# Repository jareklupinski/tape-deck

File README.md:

# tape-deck
a user-unfriendly design

```
to play music, just give it a tape.
tape-deck plays to end of the tape,
reverses, and plays the other side.
```

```
HOW DOES ONE PAUSE / STOP THE TAPE?
you should finish what you started.
```

```
HOW DO I MAKE IT LOUDER OR QUIETER?
listen to louder or quieter albums.
```

```
CAN I FASTFORWARD OR REWIND AT ALL?
the artists who recorded this album
want you to listen to it like this.
```

thank you

# MAKING OF

Circuit Board Design

Schematic

Enclosure

Code
Derived from https://github.com/elehobica/pico_crp42602y_ctrl/tree/main

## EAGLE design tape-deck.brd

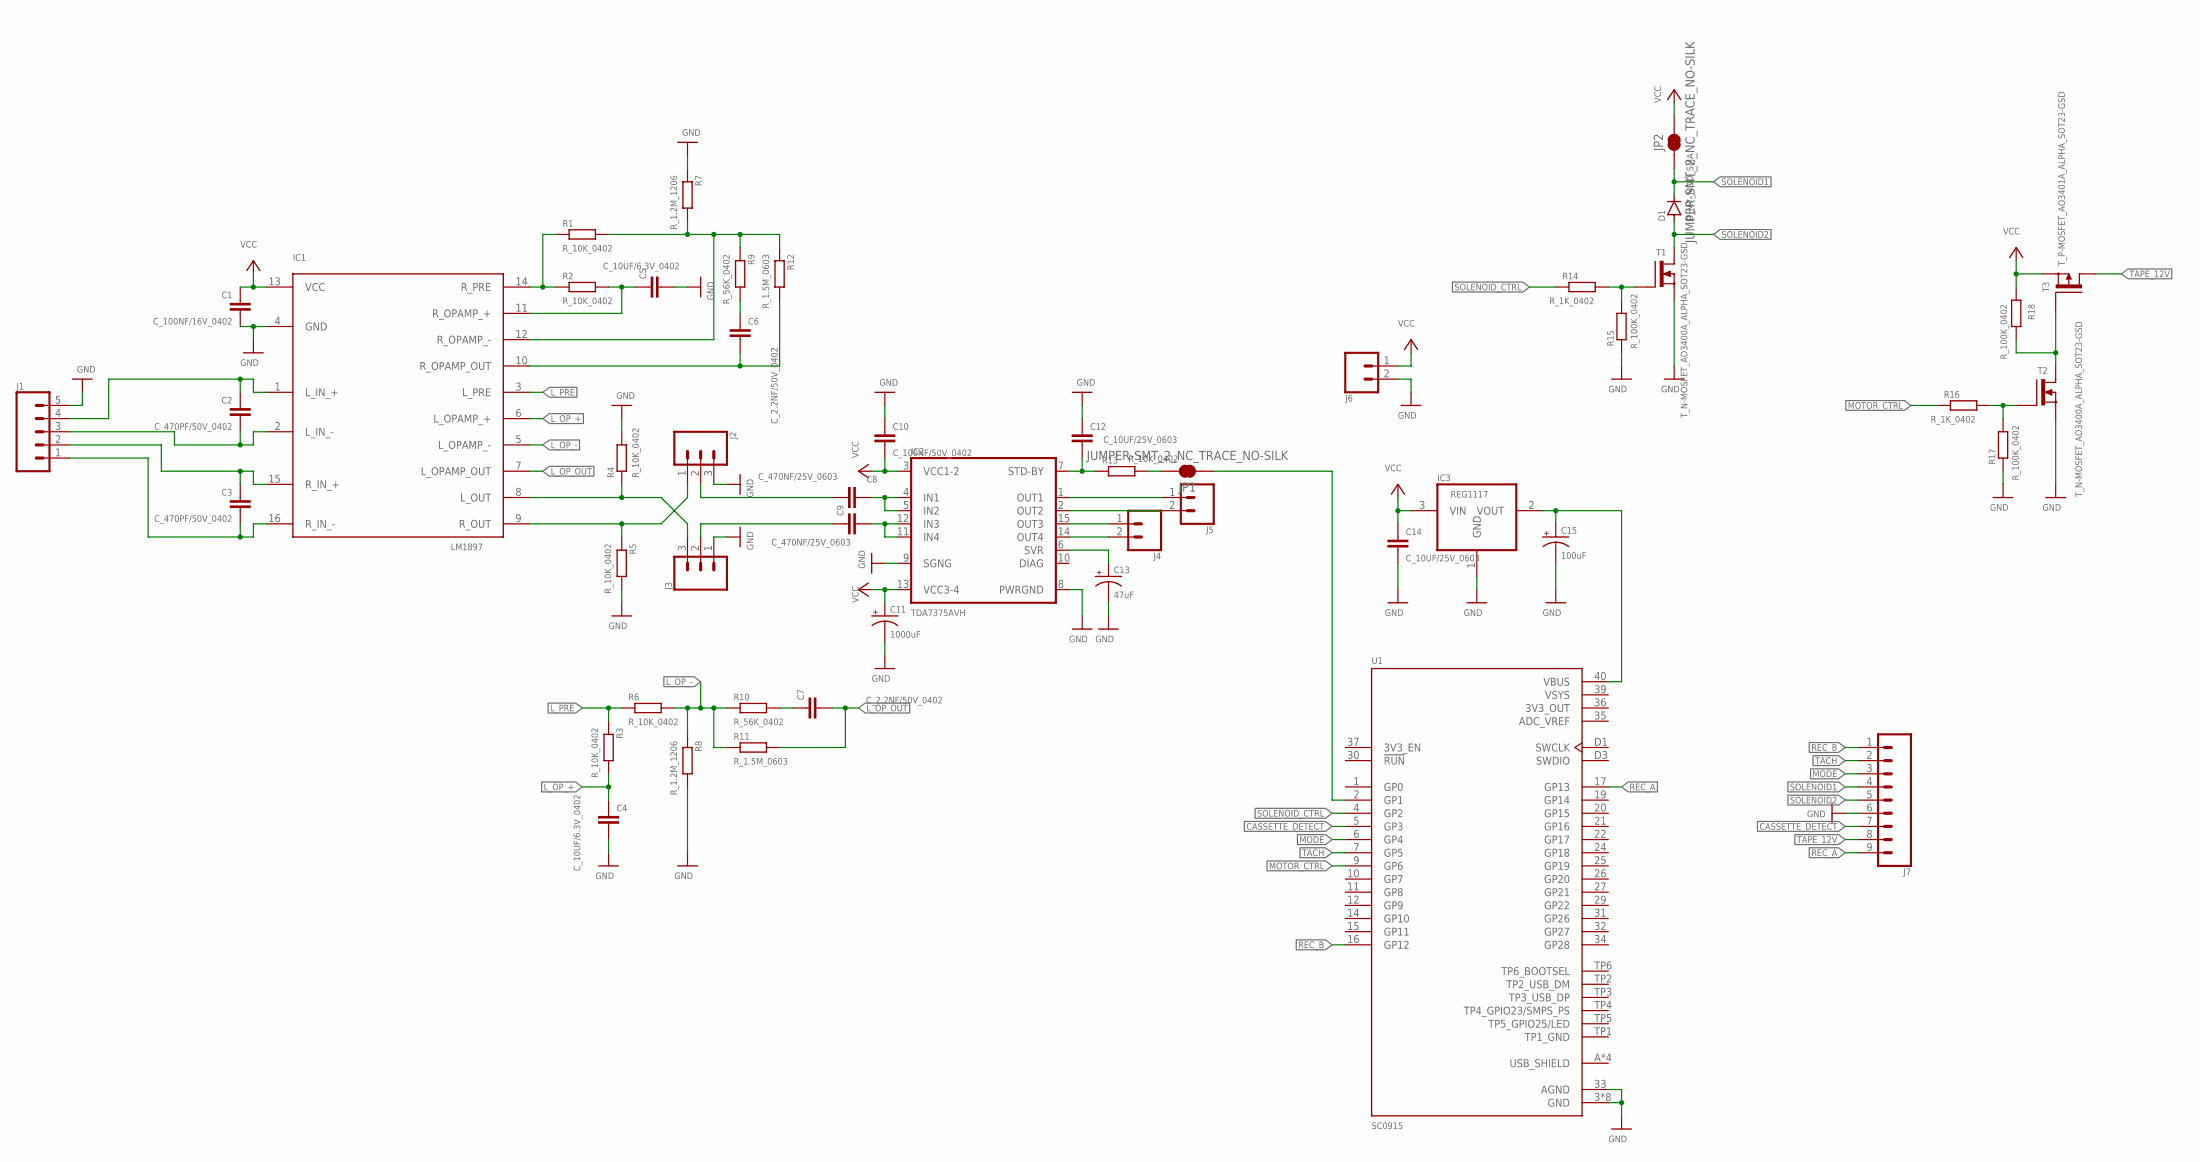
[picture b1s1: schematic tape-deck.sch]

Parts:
C1: C_100NF/16V_0402; C0402
C2, C3: C_470PF/50V_0402; C0402
C4, C5: C_10UF/6.3V_0402; C0402
C6, C7: C_2.2NF/50V_0402; C0402
C8, C9: C_470NF/25V_0603; C0603
C10: C_100NF/50V_0402; C0402
C11: 1000uF; 140CLH-1014
C12, C14: C_10UF/25V_0603; C0603
C13: 47uF; 140CLH-1014
C15: 100uF; 140CLH-1014
D1: D_M7_MDD_SMA; DO-214AC
IC1: LM1897; DIL16
IC2: TDA7375AVH; MULTIWATT-15H
IC3: REG1117; SOT223
J1: CONN_05PTH_LONGPADS; 1X05_LONGPADS
J2, J3: CONN_03; 1X03
J4, J5, J6: CONN_02LOCK_LONGPADS; 1X02_LOCK_LONGPADS
J7: CONN_09LONGPADS; 1X09_LONGPADS
JP1, JP2: JUMPER-SMT_2_NC_TRACE_NO-SILK; SMT-JUMPER_2_NC_TRACE_NO-SILK
R1, R2, R3, R4, R5, R6, R13: R_10K_0402; R0402
R7, R8: R_1.2M_1206; R1206
R9, R10: R_56K_0402; R0402
R11, R12: R_1.5M_0603; R0603
R14, R16: R_1K_0402; R0402
R15, R17, R18: R_100K_0402; R0402
T1, T2: T_N-MOSFET_AO3400A_ALPHA_SOT23-GSD; SOT23
T3: T_P-MOSFET_AO3401A_ALPHA_SOT23-GSD; SOT23
U1: SC0915; MODULE_SC0915

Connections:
3V3_OUT: U1.36 (3V3_OUT)
ADC_VREF: U1.35 (ADC_VREF)
CASSETTE_DETECT: J7.7, U1.5 (GP3)
GND: C1.2, C4.2, C5.2, C10.1, C11.-, C12.1, C13.-, C14.2, C15.-, IC1.4 (GND), IC2.8 (PWRGND), IC2.9 (SGNG), IC3.1 (GND), J1.5, J2.3, J3.1, J6.2, J7.6, R4.2, R5.2, R7.1, R8.2, R15.1, R17.1, T1.2 (S), T2.2 (S), U1.3 (GND), U1.8 (GND), U1.13 (GND), U1.18 (GND), U1.23 (GND), U1.28 (GND), U1.33 (AGND), U1.38 (GND), U1.D2 (GND)
L_OP_+: C4.1, IC1.6 (L_OPAMP_+), R3.2
L_OP_-: IC1.5 (L_OPAMP_-), R6.2, R8.1, R10.1, R11.1
L_OP_OUT: C7.2, IC1.7 (L_OPAMP_OUT), R11.2
L_PRE: IC1.3 (L_PRE), R3.1, R6.1
MODE: J7.3, U1.6 (GP4)
MOTOR_CTRL: R16.1, U1.9 (GP6)
unnamed: R14.2, R15.2, T1.1 (G)
unnamed: R16.2, R17.2, T2.1 (G)
unnamed: R18.1, T2.3 (D), T3.1 (G)
unnamed: C13.+, IC2.6 (SVR)
unnamed: C8.2, IC2.4 (IN1), IC2.5 (IN2)
unnamed: C9.2, IC2.11 (IN4), IC2.12 (IN3)
unnamed: JP1.2, R13.2
unnamed: C2.1, IC1.1 (L_IN_+), J1.4
unnamed: C2.2, IC1.2 (L_IN_-), J1.3
unnamed: C3.1, IC1.15 (R_IN_+), J1.2
unnamed: C15.+, IC3.2 (VOUT), U1.40 (VBUS)
unnamed: C3.2, IC1.16 (R_IN_-), J1.1
unnamed: JP1.1, U1.2 (GP1)
unnamed: C12.2, IC2.7 (STD-BY), R13.1
unnamed: IC2.1 (OUT1), J5.1
unnamed: IC2.2 (OUT2), J5.2
unnamed: IC2.15 (OUT3), J4.1
unnamed: IC2.14 (OUT4), J4.2
unnamed: IC1.14 (R_PRE), R1.1, R2.1
unnamed: C5.1, IC1.11 (R_OPAMP_+), R2.2
unnamed: IC1.12 (R_OPAMP_-), R1.2, R7.2, R9.1, R12.1
unnamed: C6.1, R9.2
unnamed: C7.1, R10.2
unnamed: C6.2, IC1.10 (R_OPAMP_OUT), R12.2
unnamed: IC1.8 (L_OUT), J3.3, R4.1
unnamed: IC1.9 (R_OUT), J2.1, R5.1
unnamed: C9.1, J3.2
unnamed: C8.1, J2.2
REC_A: J7.9, U1.17 (GP13)
REC_B: J7.1, U1.16 (GP12)
SOLENOID1: D1.C, J7.4, JP2.1
SOLENOID2: D1.A, J7.5, T1.3 (D)
SOLENOID_CTRL: R14.1, U1.4 (GP2)
TACH: J7.2, U1.7 (GP5)
TAPE_12V: J7.8, T3.3 (D)
TP1_GND: U1.TP1 (TP1_GND)
USB_SHIELD: U1.A (USB_SHIELD), U1.B (USB_SHIELD), U1.C (USB_SHIELD), U1.D (USB_SHIELD)
VCC: C1.1, C10.2, C11.+, C14.1, IC1.13 (VCC), IC2.3 (VCC1-2), IC2.13 (VCC3-4), IC3.3 (VIN), J6.1, JP2.2, R18.2, T3.2 (S)
VSYS: U1.39 (VSYS)

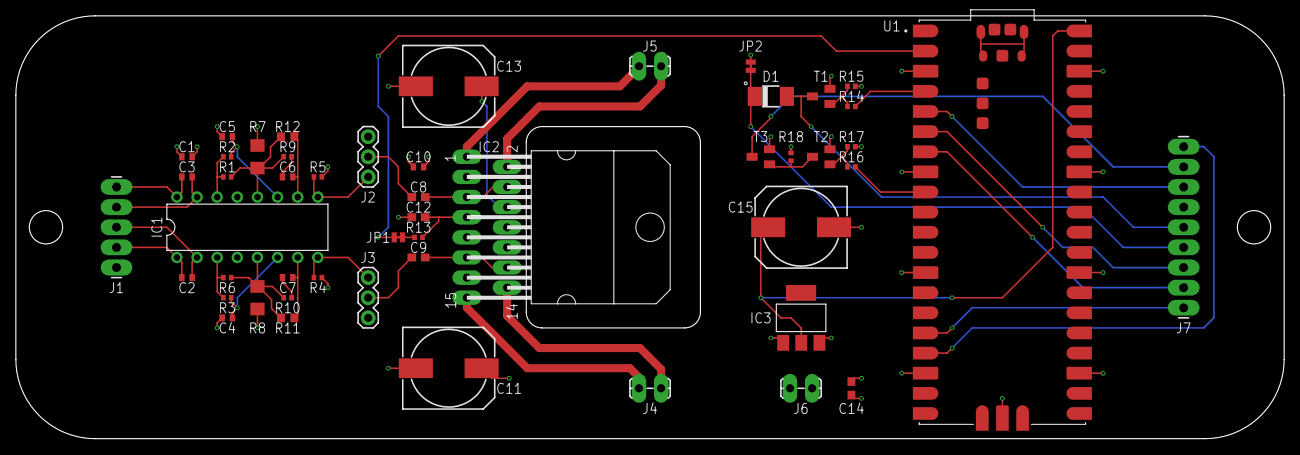
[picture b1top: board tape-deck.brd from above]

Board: 4 copper layers, 160.0 x 53.3 mm, 50 parts (0 on the bottom side), 45 nets.

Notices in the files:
parts and their libraries:
SparkFun-Connectors: Licensing: Creative Commons ShareAlike 4.0 International - https://creativecommons.org/licenses/by-sa/4.0
